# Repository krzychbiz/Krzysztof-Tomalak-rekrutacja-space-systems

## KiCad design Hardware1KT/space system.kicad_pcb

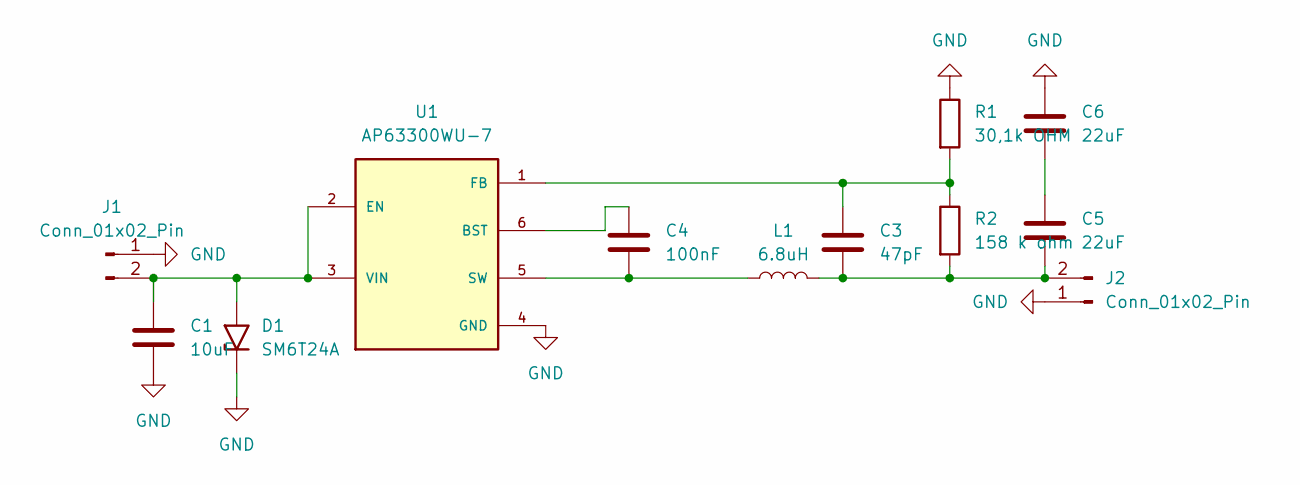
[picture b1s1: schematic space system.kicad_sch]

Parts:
C1: 10uF; LED_1206_3216Metric
C3: 47pF; C_0805_2012Metric
C4: 100nF; C_0201_0603Metric
C5, C6: 22uF; C_0805_2012Metric
D1: SM6T24A; D_SMB
J1, J2: Conn_01x02_Pin; PinHeader_1x02_P2.54mm_Vertical
L1: 6.8uH; L_APV_APH0630
R1: 30,1k OHM; R_0201_0603Metric
R2: 158 k ohm; R_0201_0603Metric
U1: AP63300WU-7; TSOT-23-6; PARTREV 2020-04-24

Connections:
GND: C1.2, C6.2, D1.1 (A1), J1.1, J2.1, R1.1, U1.4 (GND)
unnamed: C5.2, C6.1
unnamed: C1.1, D1.2 (A2), J1.2, U1.2 (EN), U1.3 (VIN)
unnamed: C3.1, C5.1, J2.2, L1.2, R2.2
unnamed: C4.1, U1.6 (BST)
unnamed: C3.2, R1.2, R2.1, U1.1 (FB)
unnamed: C4.2, L1.1, U1.5 (SW)

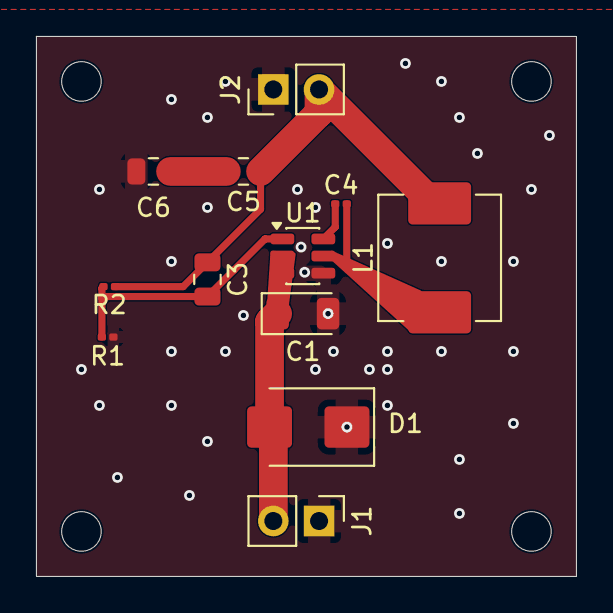
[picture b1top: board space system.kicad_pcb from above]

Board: 2 copper layers, 30.0 x 30.0 mm, 12 parts (0 on the bottom side), 7 nets.
